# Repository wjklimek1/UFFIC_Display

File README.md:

# UFFIC_Display
Ultra Fast Inter Integrated Circuit Display

UFIIC Display converts I2C serial data to HD44780 display commands. It can be powered from 3.3V or 5V power source. In case of using 3.3V power source internal step-up converter is used to boost voltage to 5V required to power HD44780 itself. Converter is based on cheap STM32F030F4P6 microcontroller that can be programmed and debuged via SWD interface.

Project is at early stage of development now, code for UFIIC and Arduino library will be provided in the future.

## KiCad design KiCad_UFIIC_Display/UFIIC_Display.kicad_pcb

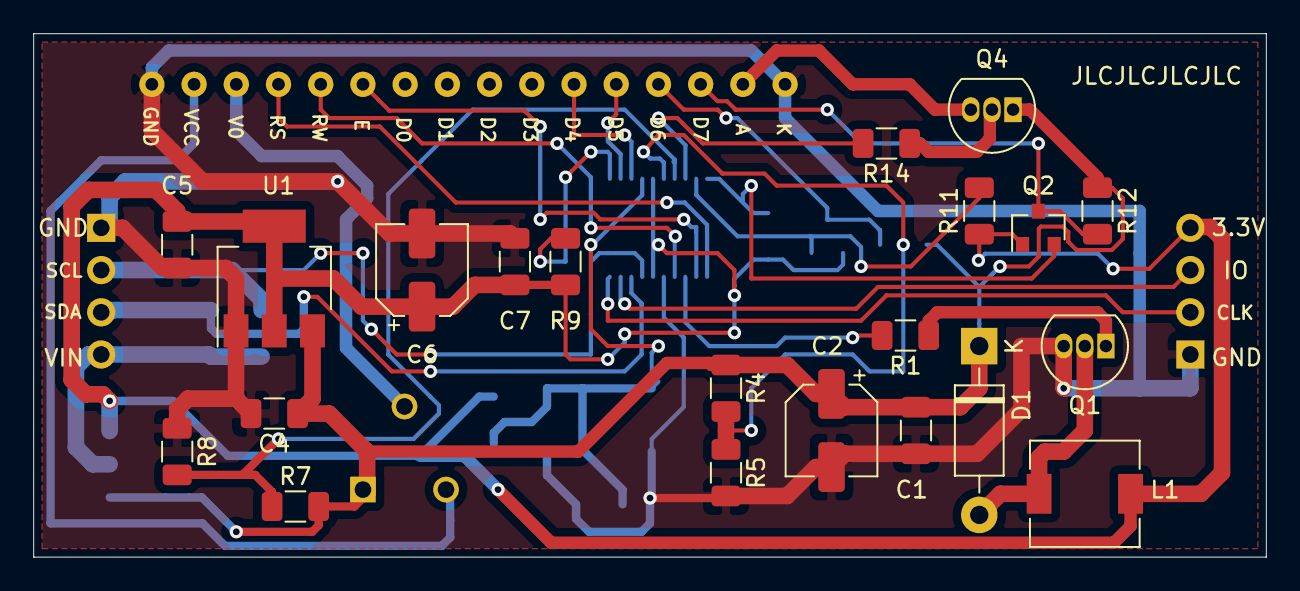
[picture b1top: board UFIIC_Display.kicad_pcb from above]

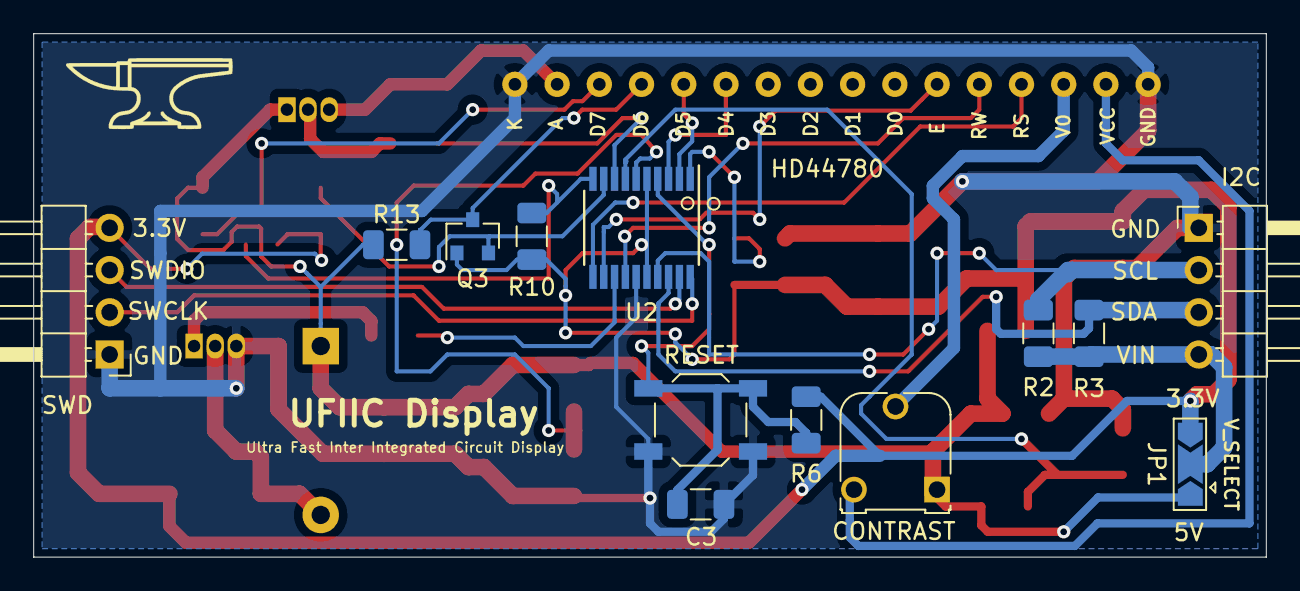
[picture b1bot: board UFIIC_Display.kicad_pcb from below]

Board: 2 copper layers, 74.2 x 31.5 mm, 35 parts (13 on the bottom side), 29 nets.

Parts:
C1, C3, C4, C5, C7: 100n; C_1206_3216Metric
C2, C6: 47u; CP_Elec_5x4.4
CONTRAST: 1K; Potentiometer_Runtron_RM-065_Vertical
D1: UF4007; D_DO-41_SOD81_P10.16mm_Horizontal
HD44780: HD44780
I2C: I2C; PinHeader_1x04_P2.54mm_Horizontal
JP1: VIN_SELECT; SolderJumper-3_P2.0mm_Open_TrianglePad1.0x1.5mm
L1: 100uH; L_6.3x6.3_H3
Q1: BC639; TO-92_Inline
Q2, Q3: BSS138; SOT-23
Q4: BC547; TO-92_Inline
R1, R6, R7, R8, R9, R14: 1K; R_1206_3216Metric
R2, R3: 4.7K; R_1206_3216Metric
R4: 3.3K; R_1206_3216Metric
R5: 820R; R_1206_3216Metric
R10, R11, R12, R13: 10K; R_1206_3216Metric
RESET: SW_Push; SW_SPST_TL3342
SWD: SWD; PinHeader_1x04_P2.54mm_Horizontal
U1: AMS1117-3.3; SOT-223-3_TabPin2
U2: STM32F030F4P6; TSSOP-20_4.4x6.5mm_P0.65mm

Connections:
+3V3: C5.1, C6.1, C7.1, JP1.3, L1.1, Q2.1, Q3.1, R6.1, R9.1, R10.1, R11.1, SWD.4, U1.2, U2.5, U2.16
/+5V: C1.1, C2.1, C4.1, CONTRAST.1, D1.1, JP1.1, Q4.1, R4.1, R7.2, R12.1, R13.1, U1.3
/ADC_DETECT: R7.1, R8.2, U2.7
/ADC_FEEDBACK: R4.2, R5.1, U2.6
/BACKLIGHT: R14.2, U2.8
/I2C1_SCL: I2C.2, R2.1, U2.17
/I2C1_SDA: I2C.3, R3.1, U2.18
/LCD_D4: HD44780.D4, U2.3
/LCD_D5: HD44780.D5, U2.2
/LCD_D6: Q3.2, R11.2, U2.9
/LCD_D7: Q2.2, R10.2, U2.10
/LCD_E: HD44780.E, U2.12
/LCD_RS: HD44780.RS, U2.11
/LCD_RW: HD44780.RW, U2.14
/PWM: R1.2, U2.13
/SWCLK: SWD.2, U2.20
/SWDIO: SWD.3, U2.19
/VIN: I2C.4, JP1.2, R2.2, R3.2
GND: C1.2, C2.2, C3.2, C4.2, C5.2, C6.2, C7.2, HD44780.GND, HD44780.K, I2C.1, Q1.3, R5.2, R8.1, RESET.1, SWD.1, U1.1, U2.15
unnamed: C3.1, R6.2, RESET.2, U2.4
unnamed: D1.2, L1.2, Q1.2
unnamed: Q1.1, R1.1
unnamed: HD44780.D7, Q2.3, R12.2
unnamed: HD44780.D6, Q3.3, R13.2
unnamed: Q4.2, R14.1
unnamed: HD44780.A, Q4.3
unnamed: R9.2, U2.1
unnamed: CONTRAST.2, HD44780.V0
unnamed: CONTRAST.3, HD44780.VCC

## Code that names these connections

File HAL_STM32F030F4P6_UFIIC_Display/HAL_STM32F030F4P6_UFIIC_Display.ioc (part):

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Mcu.Name=STM32F030F4Px
Mcu.Package=TSSOP20
Mcu.UserName=STM32F030F4Px
PA0.GPIOParameters=GPIO_Label
PA0.GPIO_Label=ADC_FEEDBACK
PA0.Mode=IN0
PA0.Signal=ADC_IN0
PA1.GPIOParameters=GPIO_Label
PA1.GPIO_Label=ADC_DETECT
PA1.Mode=IN1
PA1.Signal=ADC_IN1
PA10.Mode=I2C
PA10.Signal=I2C1_SDA
PA13.Mode=Serial_Wire
PA13.Signal=SYS_SWDIO
PA14.Mode=Serial_Wire
PA14.Signal=SYS_SWCLK
PA2.GPIOParameters=GPIO_Label
PA2.GPIO_Label=BACKLIGHT
PA2.Signal=GPIO_Output
PA3.GPIOParameters=GPIO_Label
PA3.GPIO_Label=LCD_D6
PA3.Signal=GPIO_Output
PA4.GPIOParameters=GPIO_Label
PA4.GPIO_Label=LCD_D7
PA4.Signal=GPIO_Output
PA5.GPIOParameters=GPIO_Label
PA5.GPIO_Label=LCD_RS
PA5.Signal=GPIO_Output
PA6.GPIOParameters=GPIO_Label
PA6.GPIO_Label=LCD_E
PA6.Signal=GPIO_Output
PA7.GPIOParameters=GPIO_Label
PA7.GPIO_Label=PWM
PA7.Signal=S_TIM17_CH1
PA9.Mode=I2C
PA9.Signal=I2C1_SCL
PB1.GPIOParameters=GPIO_Label
PB1.GPIO_Label=LCD_RW
PB1.Signal=GPIO_Output
PF0-OSC_IN.GPIOParameters=GPIO_Label
PF0-OSC_IN.GPIO_Label=LCD_D5
PF0-OSC_IN.Signal=GPIO_Output
PF1-OSC_OUT.GPIOParameters=GPIO_Label
PF1-OSC_OUT.GPIO_Label=LCD_D4
PF1-OSC_OUT.Signal=GPIO_Output
RCC.SYSCLKFreq_VALUE=48000000
RCC.SYSCLKSource=RCC_SYSCLKSOURCE_PLLCLK
board=custom

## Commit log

2020-06-18 KiCad schematic and PCB
    + Added KiCad schematic and PCB
    + Added .gitignore file
    + Updated readme.md file
2020-06-19 ADC read by DMA
    + Initial configuration in CubeIDE
    + ADC read by DMA
    + timer initialization
2020-06-20 Added step-up converter logic
    + Step-up voltage converter logic added to timer16 interrupt handler
2020-07-11 Backlight powered by 5V step up
    + backlight is powered by 5V step-up
    + removed unnecessary KiCad files
    + updated .gitignore
2020-07-11 HD44780 library
    + Added working HD44780 display library with busy flag support
